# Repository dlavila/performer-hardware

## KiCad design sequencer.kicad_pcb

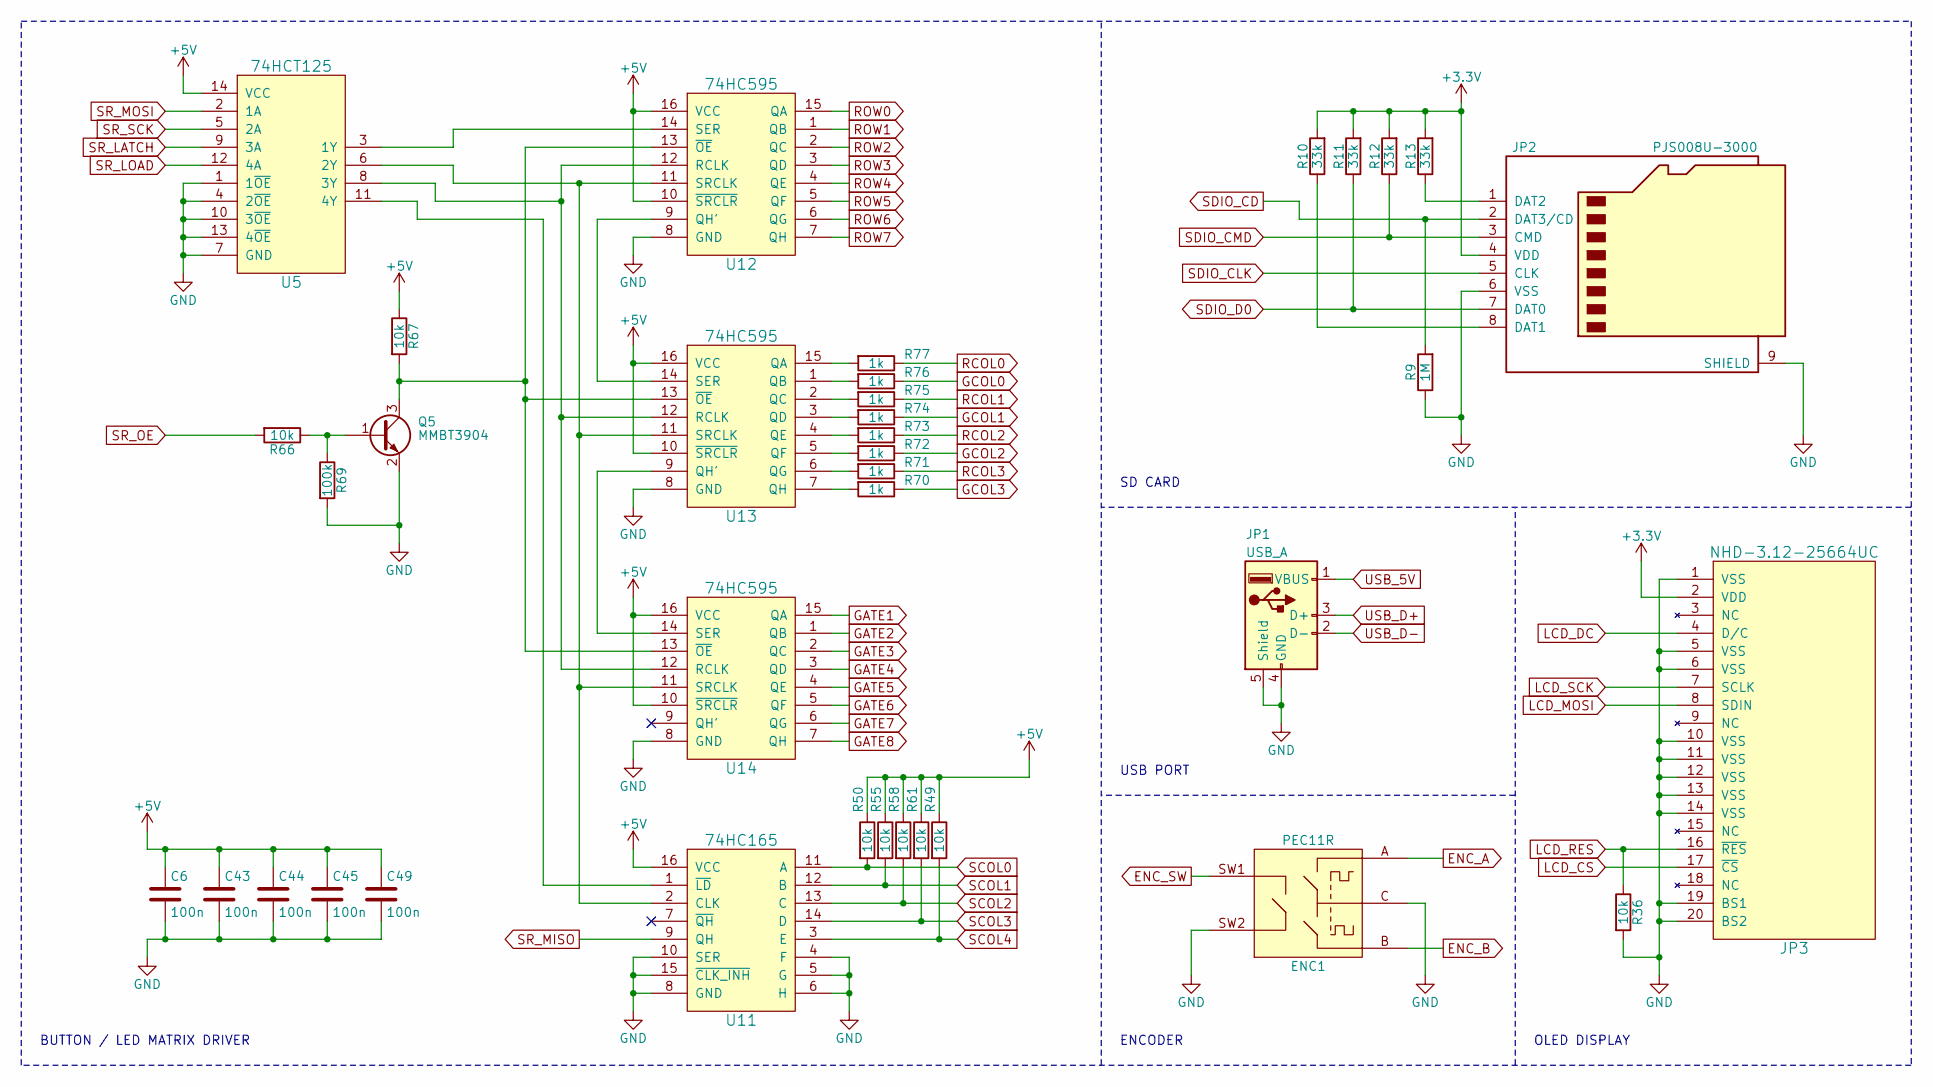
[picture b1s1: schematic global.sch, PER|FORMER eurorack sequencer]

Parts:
C6, C43, C44, C45, C49: 100n; C_0603
ENC1: PEC11R; ALPS_STEC12E08
JP1: USB_A; Kycon_USB_KUSBVLPX-AS1N
JP2: PJS008U-3000; PJS008U-3000-0
JP3: NHD-3.12-25664UC
Q5: MMBT3904; SOT-23
R9: 1M; R_0603
R10, R11, R12, R13: 33k; R_0603
R36, R49, R50, R55, R58, R61, R66, R67: 10k; R_0603
R69: 100k; R_0603
R70, R71, R72, R73, R74, R75, R76, R77: 1k; R_0603
U5: 74HCT125; SOIC-14_3.9x8.7mm_P1.27mm
U11: 74HC165; SOIC-16
U12, U13, U14: 74HC595; SOIC-16

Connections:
ENC_A: ENC1.A; also elsewhere on the board
ENC_B: ENC1.B; also elsewhere on the board
ENC_SW: ENC1.SW1; also elsewhere on the board
GATE1: U14.15 (QA); also elsewhere on the board
GATE2: U14.1 (QB); also elsewhere on the board
GATE3: U14.2 (QC); also elsewhere on the board
GATE4: U14.3 (QD); also elsewhere on the board
GATE5: U14.4 (QE); also elsewhere on the board
GATE6: U14.5 (QF); also elsewhere on the board
GATE7: U14.6 (QG); also elsewhere on the board
GATE8: U14.7 (QH); also elsewhere on the board
GCOL0: R76.1; also elsewhere on the board
GCOL1: R74.1; also elsewhere on the board
GCOL2: R72.1; also elsewhere on the board
GCOL3: R70.1; also elsewhere on the board
LCD_CS: JP3.17 (~CS); also elsewhere on the board
LCD_DC: JP3.4 (D/C); also elsewhere on the board
LCD_MOSI: JP3.8 (SDIN); also elsewhere on the board
LCD_RES: JP3.16 (~RES), R36.1; also elsewhere on the board
LCD_SCK: JP3.7 (SCLK); also elsewhere on the board
unnamed: JP2.1 (DAT2), R13.1
unnamed: JP2.8 (DAT1), R10.1
unnamed: Q5.1 (B), R66.1, R69.1
unnamed: Q5.3 (C), R67.2, U12.13 (~OE~), U13.13 (~OE~), U14.13 (~OE~)
unnamed: R70.2, U13.7 (QH)
unnamed: R71.2, U13.6 (QG)
unnamed: R72.2, U13.5 (QF)
unnamed: R73.2, U13.4 (QE)
unnamed: R74.2, U13.3 (QD)
unnamed: R75.2, U13.2 (QC)
unnamed: R76.2, U13.1 (QB)
unnamed: R77.2, U13.15 (QA)
unnamed: U5.11 (4Y), U11.1 (~LD~)
unnamed: U5.6 (2Y), U11.2 (CLK), U12.11 (SRCLK), U13.11 (SRCLK), U14.11 (SRCLK)
unnamed: U12.9 (QH'), U13.14 (SER)
unnamed: U5.8 (3Y), U12.12 (RCLK), U13.12 (RCLK), U14.12 (RCLK)
unnamed: U5.3 (1Y), U12.14 (SER)
unnamed: U13.9 (QH'), U14.14 (SER)
RCOL0: R77.1; also elsewhere on the board
RCOL1: R75.1; also elsewhere on the board
RCOL2: R73.1; also elsewhere on the board
RCOL3: R71.1; also elsewhere on the board
ROW0: U12.15 (QA); also elsewhere on the board
ROW1: U12.1 (QB); also elsewhere on the board
ROW2: U12.2 (QC); also elsewhere on the board
ROW3: U12.3 (QD); also elsewhere on the board
ROW4: U12.4 (QE); also elsewhere on the board
ROW5: U12.5 (QF); also elsewhere on the board
ROW6: U12.6 (QG); also elsewhere on the board
ROW7: U12.7 (QH); also elsewhere on the board
SCOL0: R50.2, U11.11 (A); also elsewhere on the board
SCOL1: R55.2, U11.12 (B); also elsewhere on the board
SCOL2: R58.2, U11.13 (C); also elsewhere on the board
SCOL3: R61.2, U11.14 (D); also elsewhere on the board
SCOL4: R49.2, U11.3 (E); also elsewhere on the board
SDIO_CD: JP2.2 (DAT3/CD), R9.2; also elsewhere on the board
SDIO_CLK: JP2.5 (CLK); also elsewhere on the board
SDIO_CMD: JP2.3 (CMD), R12.1; also elsewhere on the board
SDIO_D0: JP2.7 (DAT0), R11.1; also elsewhere on the board
SR_LATCH: U5.9 (3A); also elsewhere on the board
SR_LOAD: U5.12 (4A); also elsewhere on the board
SR_MISO: U11.9 (QH); also elsewhere on the board
SR_MOSI: U5.2 (1A); also elsewhere on the board
SR_OE: R66.2; also elsewhere on the board
SR_SCK: U5.5 (2A); also elsewhere on the board
USB_5V: JP1.1 (VBUS); also elsewhere on the board
USB_D+: JP1.3 (D+); also elsewhere on the board
USB_D-: JP1.2 (D-); also elsewhere on the board

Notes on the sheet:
BUTTON / LED MATRIX DRIVER
SD CARD
OLED DISPLAY
ENCODER
USB PORT

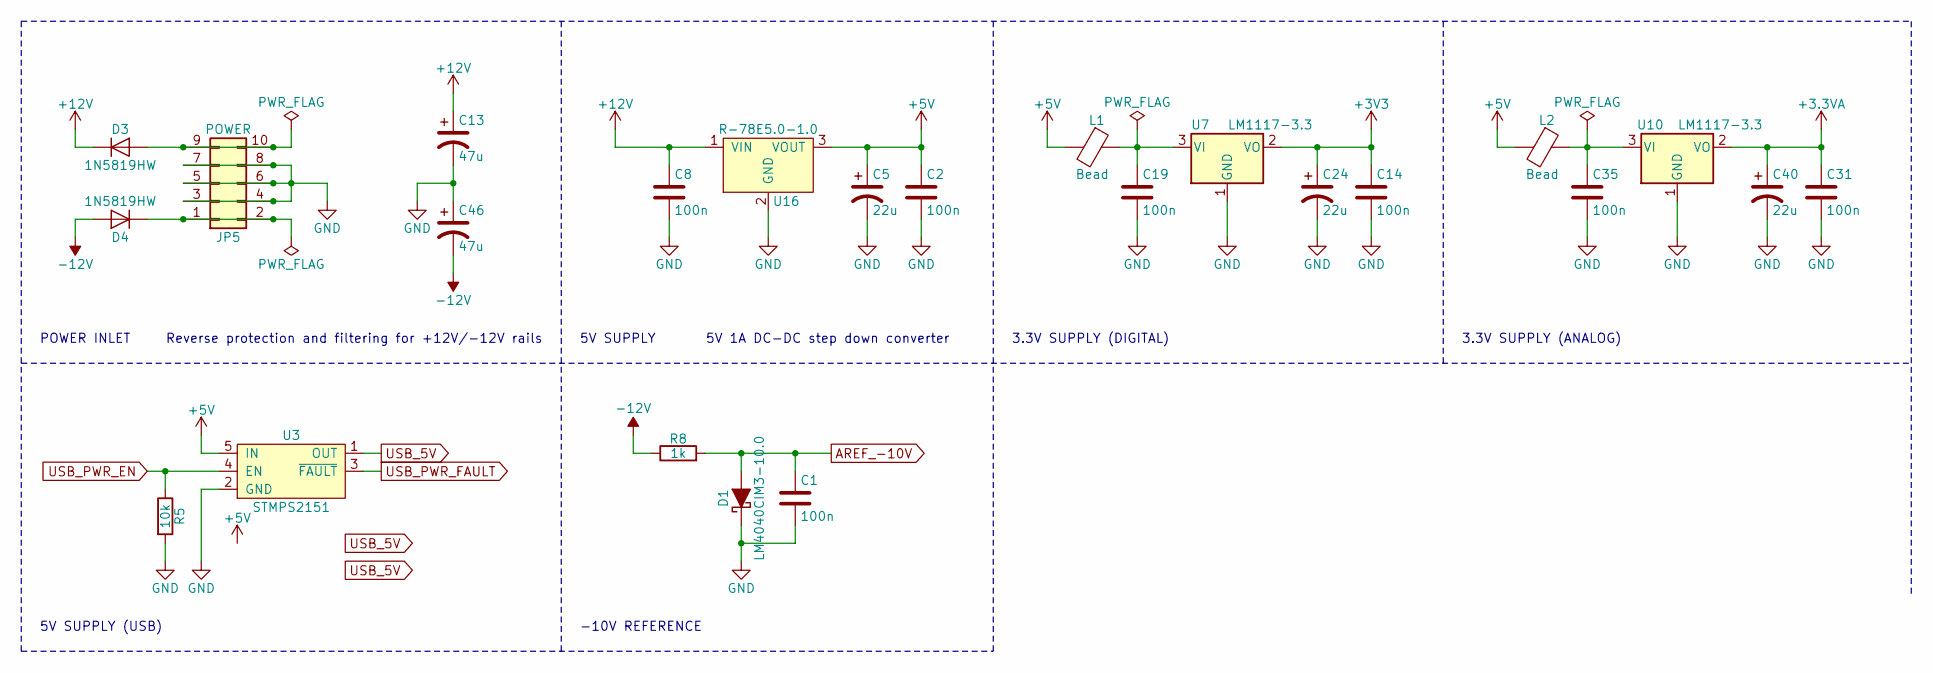
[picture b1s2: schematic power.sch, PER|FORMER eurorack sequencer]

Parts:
C1, C2, C8, C14, C19, C31, C35: 100n; C_0603
C5, C24, C40: 22u; CP_Elec_5x5.8
C13, C46: 47u; CP_Elec_6.3x5.7
D1: LM4040CIM3-10.0; SOT-23
D3, D4: 1N5819HW; D_SOD-123
JP5: POWER; PinHeader_2x05_P2.54mm_Vertical
L1, L2: Bead; R_0603
R5: 10k; R_0603
R8: 1k; R_0603
U3: STMPS2151; TSSOP-8_4.4x3mm_P0.65mm
U7, U10: LM1117-3.3; SOT-223-3_TabPin2
U16: R-78E5.0-1.0; R-78E-1.0

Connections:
+3.3VA: C31.1, C40.1, U10.2 (VO); also elsewhere on the board
+12V: C8.1, C13.1, D3.1 (K), U16.1 (VIN); also elsewhere on the board
-12V: C46.2, D4.2 (A), R8.1; also elsewhere on the board
AREF_-10V: C1.1, D1.2 (A), R8.2; also elsewhere on the board
unnamed: C19.1, L1.1, U7.3 (VI)
unnamed: C35.1, L2.1, U10.3 (VI)
unnamed: D3.2 (A), JP5.9, JP5.10
unnamed: D4.1 (K), JP5.1, JP5.2
USB_5V: U3.6, U3.7, U3.8; also elsewhere on the board
USB_PWR_EN: R5.1, U3.4 (EN); also elsewhere on the board

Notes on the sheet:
POWER INLET
Reverse protection and filtering for +12V/-12V rails
5V SUPPLY
5V 1A DC-DC step down converter
3.3V SUPPLY (DIGITAL)
3.3V SUPPLY (ANALOG)
5V SUPPLY (USB)
-10V REFERENCE

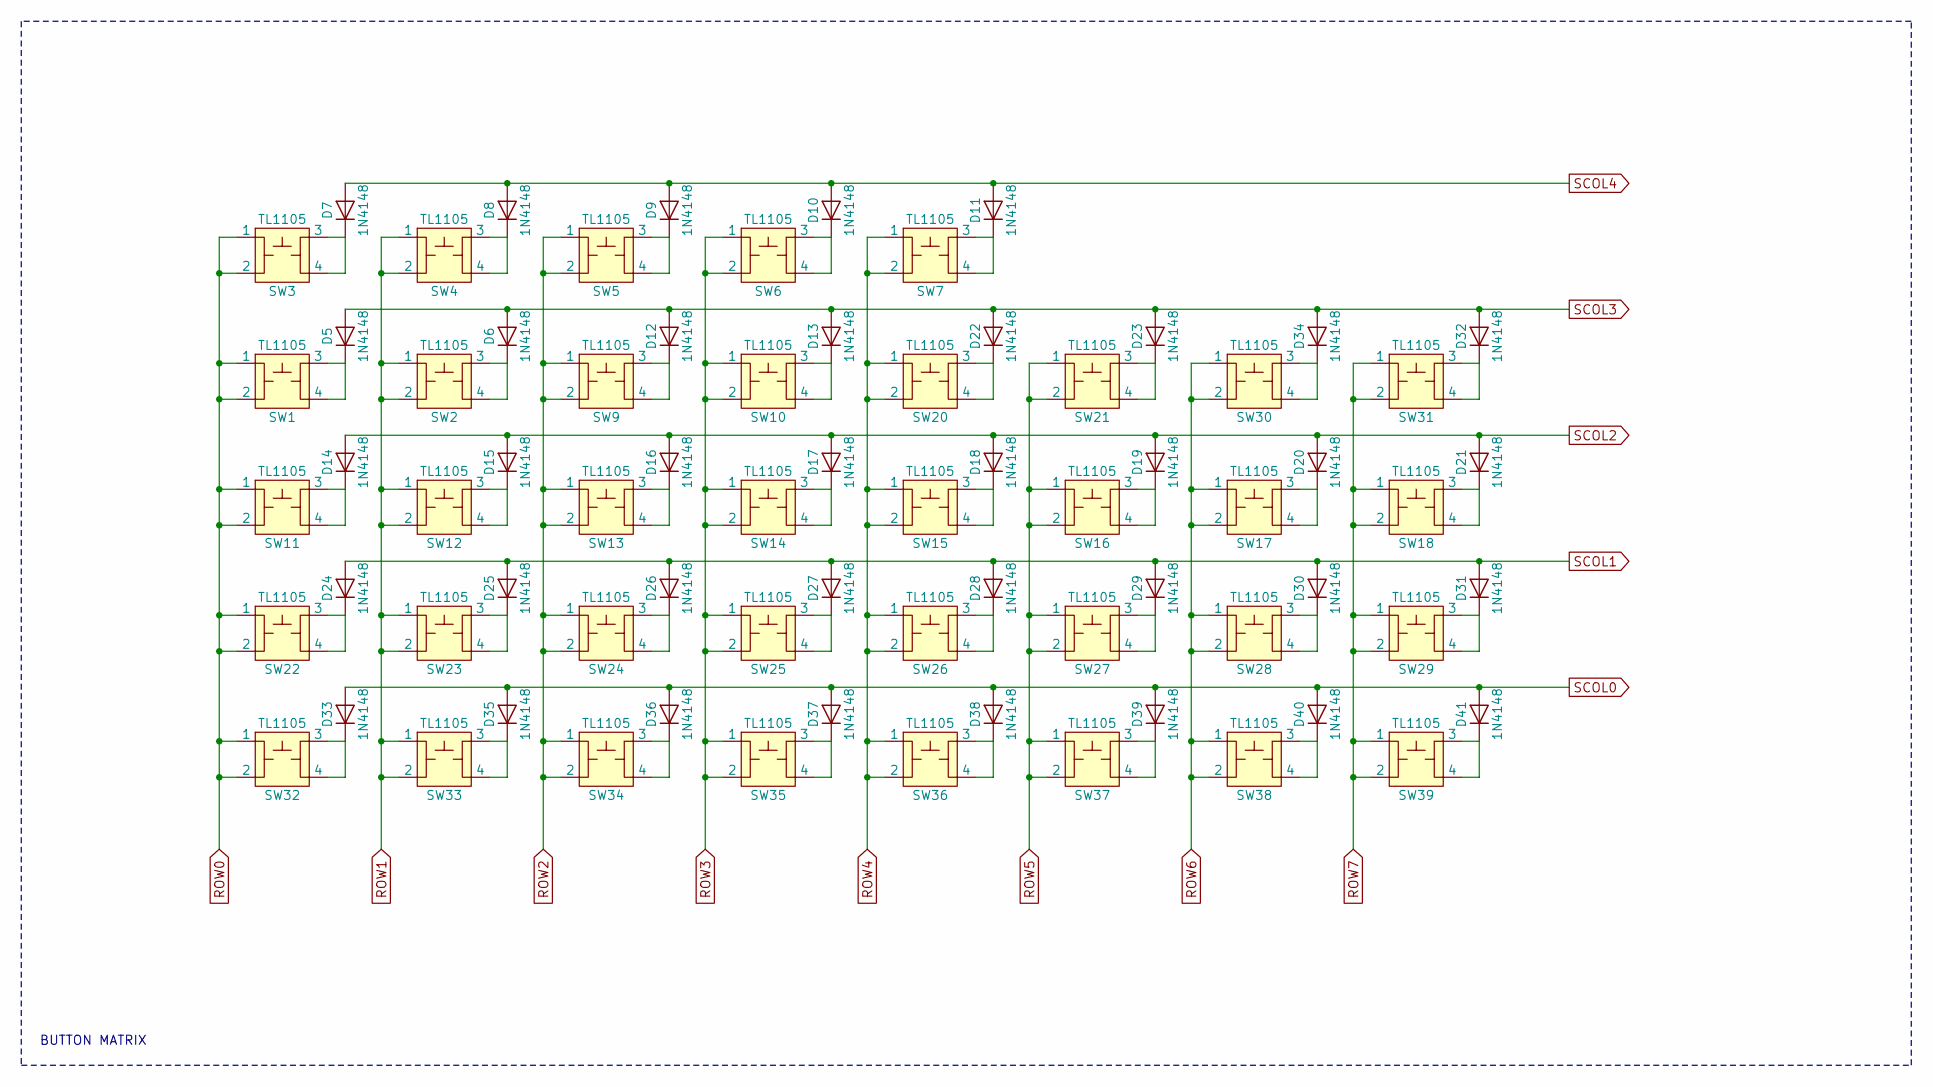
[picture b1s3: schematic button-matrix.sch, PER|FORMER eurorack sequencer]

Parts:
D5, D6, D7, D8, D9, D10, D11, D12, D13, D14, D15, D16, D17, D18, D19, D20, D21, D22, D23, D24, D25, D26, D27, D28, D29, D30, D31, D32, D33, D34, D35, D36, D37, D38, D39, D40, D41: 1N4148; D_SOD-123
SW1, SW2, SW3, SW4, SW5, SW6, SW7, SW9, SW10, SW11, SW12, SW13, SW14, SW15, SW16, SW17, SW18, SW20, SW21, SW22, SW23, SW24, SW25, SW26, SW27, SW28, SW29, SW30, SW31, SW32, SW33, SW34, SW35, SW36, SW37, SW38, SW39: TL1105; TL1105T

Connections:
unnamed: D5.1 (K), SW1.3, SW1.4
unnamed: D6.1 (K), SW2.3, SW2.4
unnamed: D7.1 (K), SW3.3, SW3.4
unnamed: D8.1 (K), SW4.3, SW4.4
unnamed: D9.1 (K), SW5.3, SW5.4
unnamed: D10.1 (K), SW6.3, SW6.4
unnamed: D11.1 (K), SW7.3, SW7.4
unnamed: D12.1 (K), SW9.3, SW9.4
unnamed: D13.1 (K), SW10.3, SW10.4
unnamed: D14.1 (K), SW11.3, SW11.4
unnamed: D15.1 (K), SW12.3, SW12.4
unnamed: D16.1 (K), SW13.3, SW13.4
unnamed: D17.1 (K), SW14.3, SW14.4
unnamed: D18.1 (K), SW15.3, SW15.4
unnamed: D19.1 (K), SW16.3, SW16.4
unnamed: D20.1 (K), SW17.3, SW17.4
unnamed: D21.1 (K), SW18.3, SW18.4
unnamed: D22.1 (K), SW20.3, SW20.4
unnamed: D23.1 (K), SW21.3, SW21.4
unnamed: D24.1 (K), SW22.3, SW22.4
unnamed: D25.1 (K), SW23.3, SW23.4
unnamed: D26.1 (K), SW24.3, SW24.4
unnamed: D27.1 (K), SW25.3, SW25.4
unnamed: D28.1 (K), SW26.3, SW26.4
unnamed: D29.1 (K), SW27.3, SW27.4
unnamed: D30.1 (K), SW28.3, SW28.4
unnamed: D31.1 (K), SW29.3, SW29.4
unnamed: D32.1 (K), SW31.3, SW31.4
unnamed: D33.1 (K), SW32.3, SW32.4
unnamed: D34.1 (K), SW30.3, SW30.4
unnamed: D35.1 (K), SW33.3, SW33.4
unnamed: D36.1 (K), SW34.3, SW34.4
unnamed: D37.1 (K), SW35.3, SW35.4
unnamed: D38.1 (K), SW36.3, SW36.4
unnamed: D39.1 (K), SW37.3, SW37.4
unnamed: D40.1 (K), SW38.3, SW38.4
unnamed: D41.1 (K), SW39.3, SW39.4
ROW0: SW1.1, SW1.2, SW3.1, SW3.2, SW11.1, SW11.2, SW22.1, SW22.2, SW32.1, SW32.2; also elsewhere on the board
ROW1: SW2.1, SW2.2, SW4.1, SW4.2, SW12.1, SW12.2, SW23.1, SW23.2, SW33.1, SW33.2; also elsewhere on the board
ROW2: SW5.1, SW5.2, SW9.1, SW9.2, SW13.1, SW13.2, SW24.1, SW24.2, SW34.1, SW34.2; also elsewhere on the board
ROW3: SW6.1, SW6.2, SW10.1, SW10.2, SW14.1, SW14.2, SW25.1, SW25.2, SW35.1, SW35.2; also elsewhere on the board
ROW4: SW7.1, SW7.2, SW15.1, SW15.2, SW20.1, SW20.2, SW26.1, SW26.2, SW36.1, SW36.2; also elsewhere on the board
ROW5: SW16.1, SW16.2, SW21.1, SW21.2, SW27.1, SW27.2, SW37.1, SW37.2; also elsewhere on the board
ROW6: SW17.1, SW17.2, SW28.1, SW28.2, SW30.1, SW30.2, SW38.1, SW38.2; also elsewhere on the board
ROW7: SW18.1, SW18.2, SW29.1, SW29.2, SW31.1, SW31.2, SW39.1, SW39.2; also elsewhere on the board
SCOL0: D33.2 (A), D35.2 (A), D36.2 (A), D37.2 (A), D38.2 (A), D39.2 (A), D40.2 (A), D41.2 (A); also elsewhere on the board
SCOL1: D24.2 (A), D25.2 (A), D26.2 (A), D27.2 (A), D28.2 (A), D29.2 (A), D30.2 (A), D31.2 (A); also elsewhere on the board
SCOL2: D14.2 (A), D15.2 (A), D16.2 (A), D17.2 (A), D18.2 (A), D19.2 (A), D20.2 (A), D21.2 (A); also elsewhere on the board
SCOL3: D5.2 (A), D6.2 (A), D12.2 (A), D13.2 (A), D22.2 (A), D23.2 (A), D32.2 (A), D34.2 (A); also elsewhere on the board
SCOL4: D7.2 (A), D8.2 (A), D9.2 (A), D10.2 (A), D11.2 (A); also elsewhere on the board

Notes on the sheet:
BUTTON MATRIX

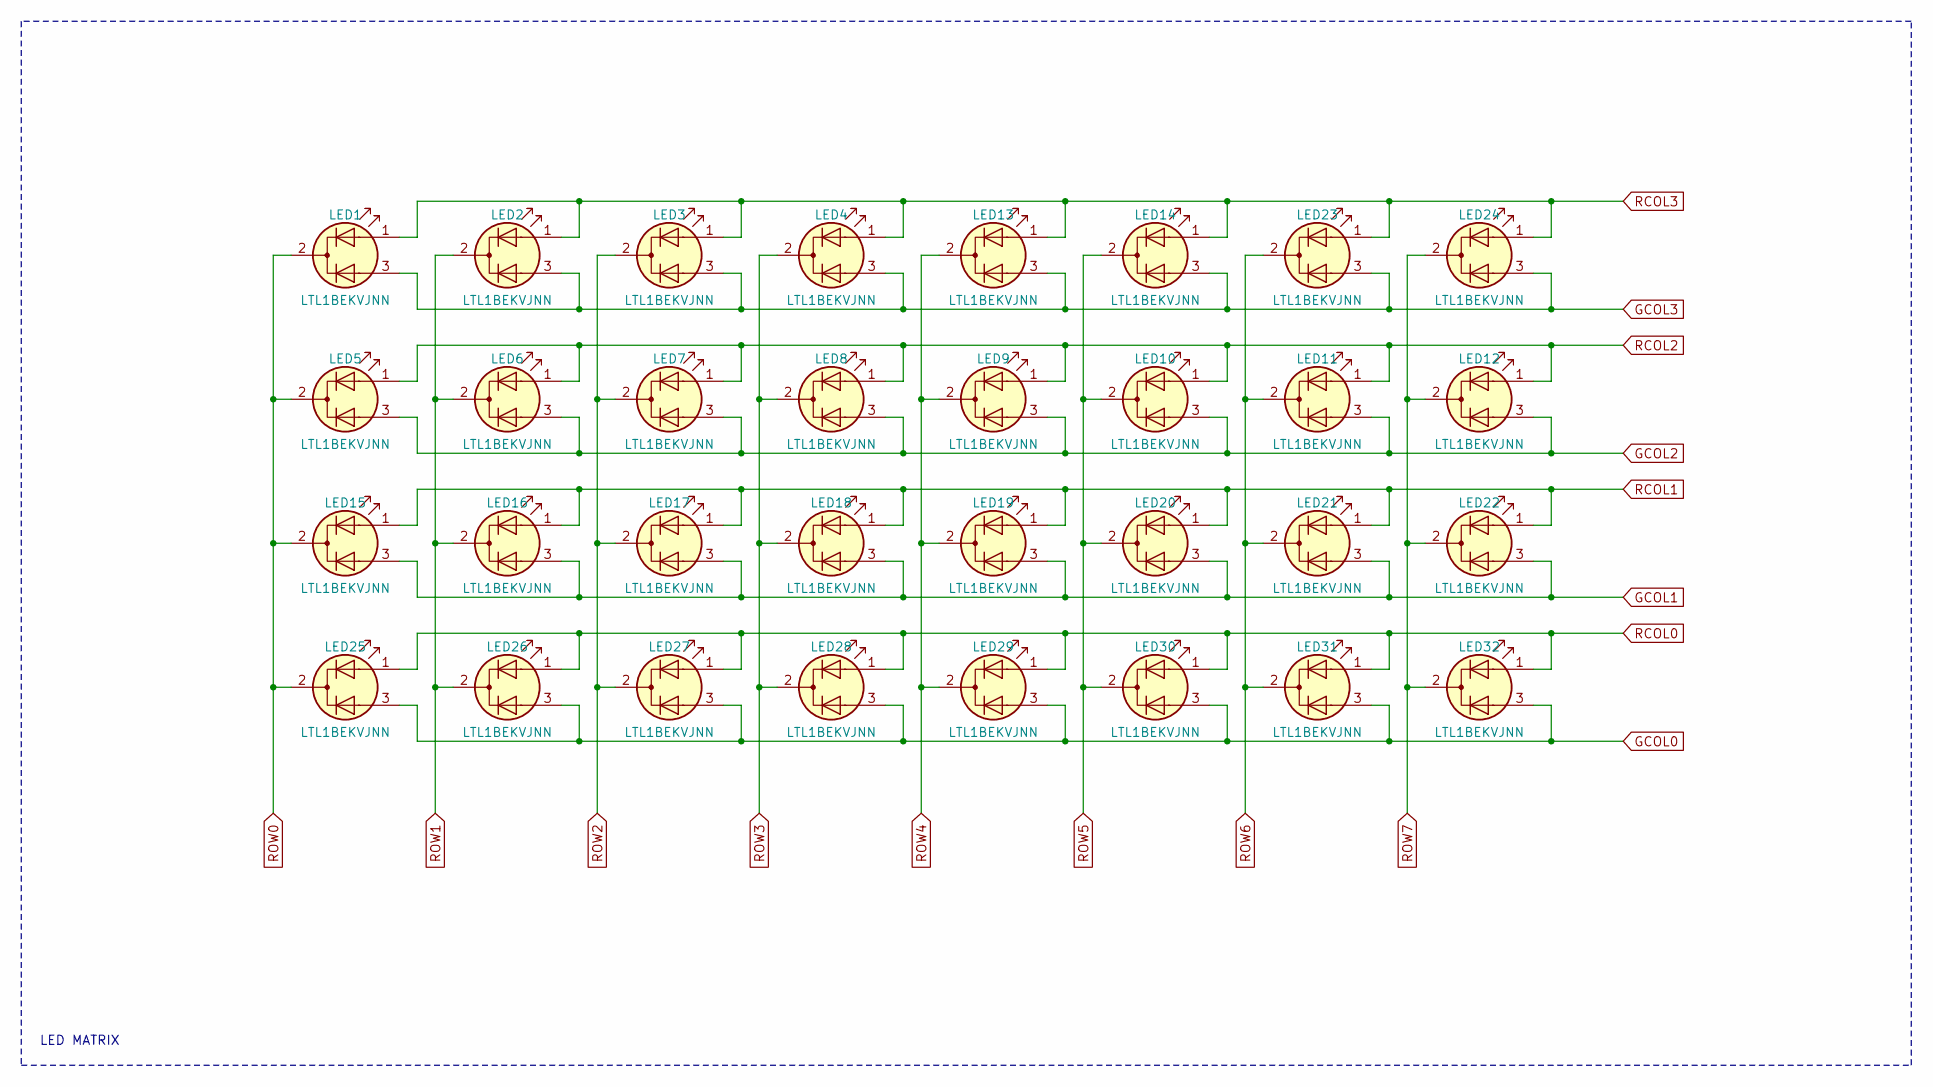
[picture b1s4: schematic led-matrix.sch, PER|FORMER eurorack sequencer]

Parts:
LED1, LED2, LED3, LED4, LED5, LED6, LED7, LED8, LED9, LED10, LED11, LED12, LED13, LED14, LED15, LED16, LED17, LED18, LED19, LED20, LED21, LED22, LED23, LED24, LED25, LED26, LED27, LED28, LED29, LED30, LED31, LED32: LTL1BEKVJNN

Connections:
GCOL0: LED25.3 (A2), LED26.3 (A2), LED27.3 (A2), LED28.3 (A2), LED29.3 (A2), LED30.3 (A2), LED31.3 (A2), LED32.3 (A2); also elsewhere on the board
GCOL1: LED15.3 (A2), LED16.3 (A2), LED17.3 (A2), LED18.3 (A2), LED19.3 (A2), LED20.3 (A2), LED21.3 (A2), LED22.3 (A2); also elsewhere on the board
GCOL2: LED5.3 (A2), LED6.3 (A2), LED7.3 (A2), LED8.3 (A2), LED9.3 (A2), LED10.3 (A2), LED11.3 (A2), LED12.3 (A2); also elsewhere on the board
GCOL3: LED1.3 (A2), LED2.3 (A2), LED3.3 (A2), LED4.3 (A2), LED13.3 (A2), LED14.3 (A2), LED23.3 (A2), LED24.3 (A2); also elsewhere on the board
RCOL0: LED25.1 (A1), LED26.1 (A1), LED27.1 (A1), LED28.1 (A1), LED29.1 (A1), LED30.1 (A1), LED31.1 (A1), LED32.1 (A1); also elsewhere on the board
RCOL1: LED15.1 (A1), LED16.1 (A1), LED17.1 (A1), LED18.1 (A1), LED19.1 (A1), LED20.1 (A1), LED21.1 (A1), LED22.1 (A1); also elsewhere on the board
RCOL2: LED5.1 (A1), LED6.1 (A1), LED7.1 (A1), LED8.1 (A1), LED9.1 (A1), LED10.1 (A1), LED11.1 (A1), LED12.1 (A1); also elsewhere on the board
RCOL3: LED1.1 (A1), LED2.1 (A1), LED3.1 (A1), LED4.1 (A1), LED13.1 (A1), LED14.1 (A1), LED23.1 (A1), LED24.1 (A1); also elsewhere on the board
ROW0: LED1.2 (K), LED5.2 (K), LED15.2 (K), LED25.2 (K); also elsewhere on the board
ROW1: LED2.2 (K), LED6.2 (K), LED16.2 (K), LED26.2 (K); also elsewhere on the board
ROW2: LED3.2 (K), LED7.2 (K), LED17.2 (K), LED27.2 (K); also elsewhere on the board
ROW3: LED4.2 (K), LED8.2 (K), LED18.2 (K), LED28.2 (K); also elsewhere on the board
ROW4: LED9.2 (K), LED13.2 (K), LED19.2 (K), LED29.2 (K); also elsewhere on the board
ROW5: LED10.2 (K), LED14.2 (K), LED20.2 (K), LED30.2 (K); also elsewhere on the board
ROW6: LED11.2 (K), LED21.2 (K), LED23.2 (K), LED31.2 (K); also elsewhere on the board
ROW7: LED12.2 (K), LED22.2 (K), LED24.2 (K), LED32.2 (K); also elsewhere on the board

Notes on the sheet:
LED MATRIX

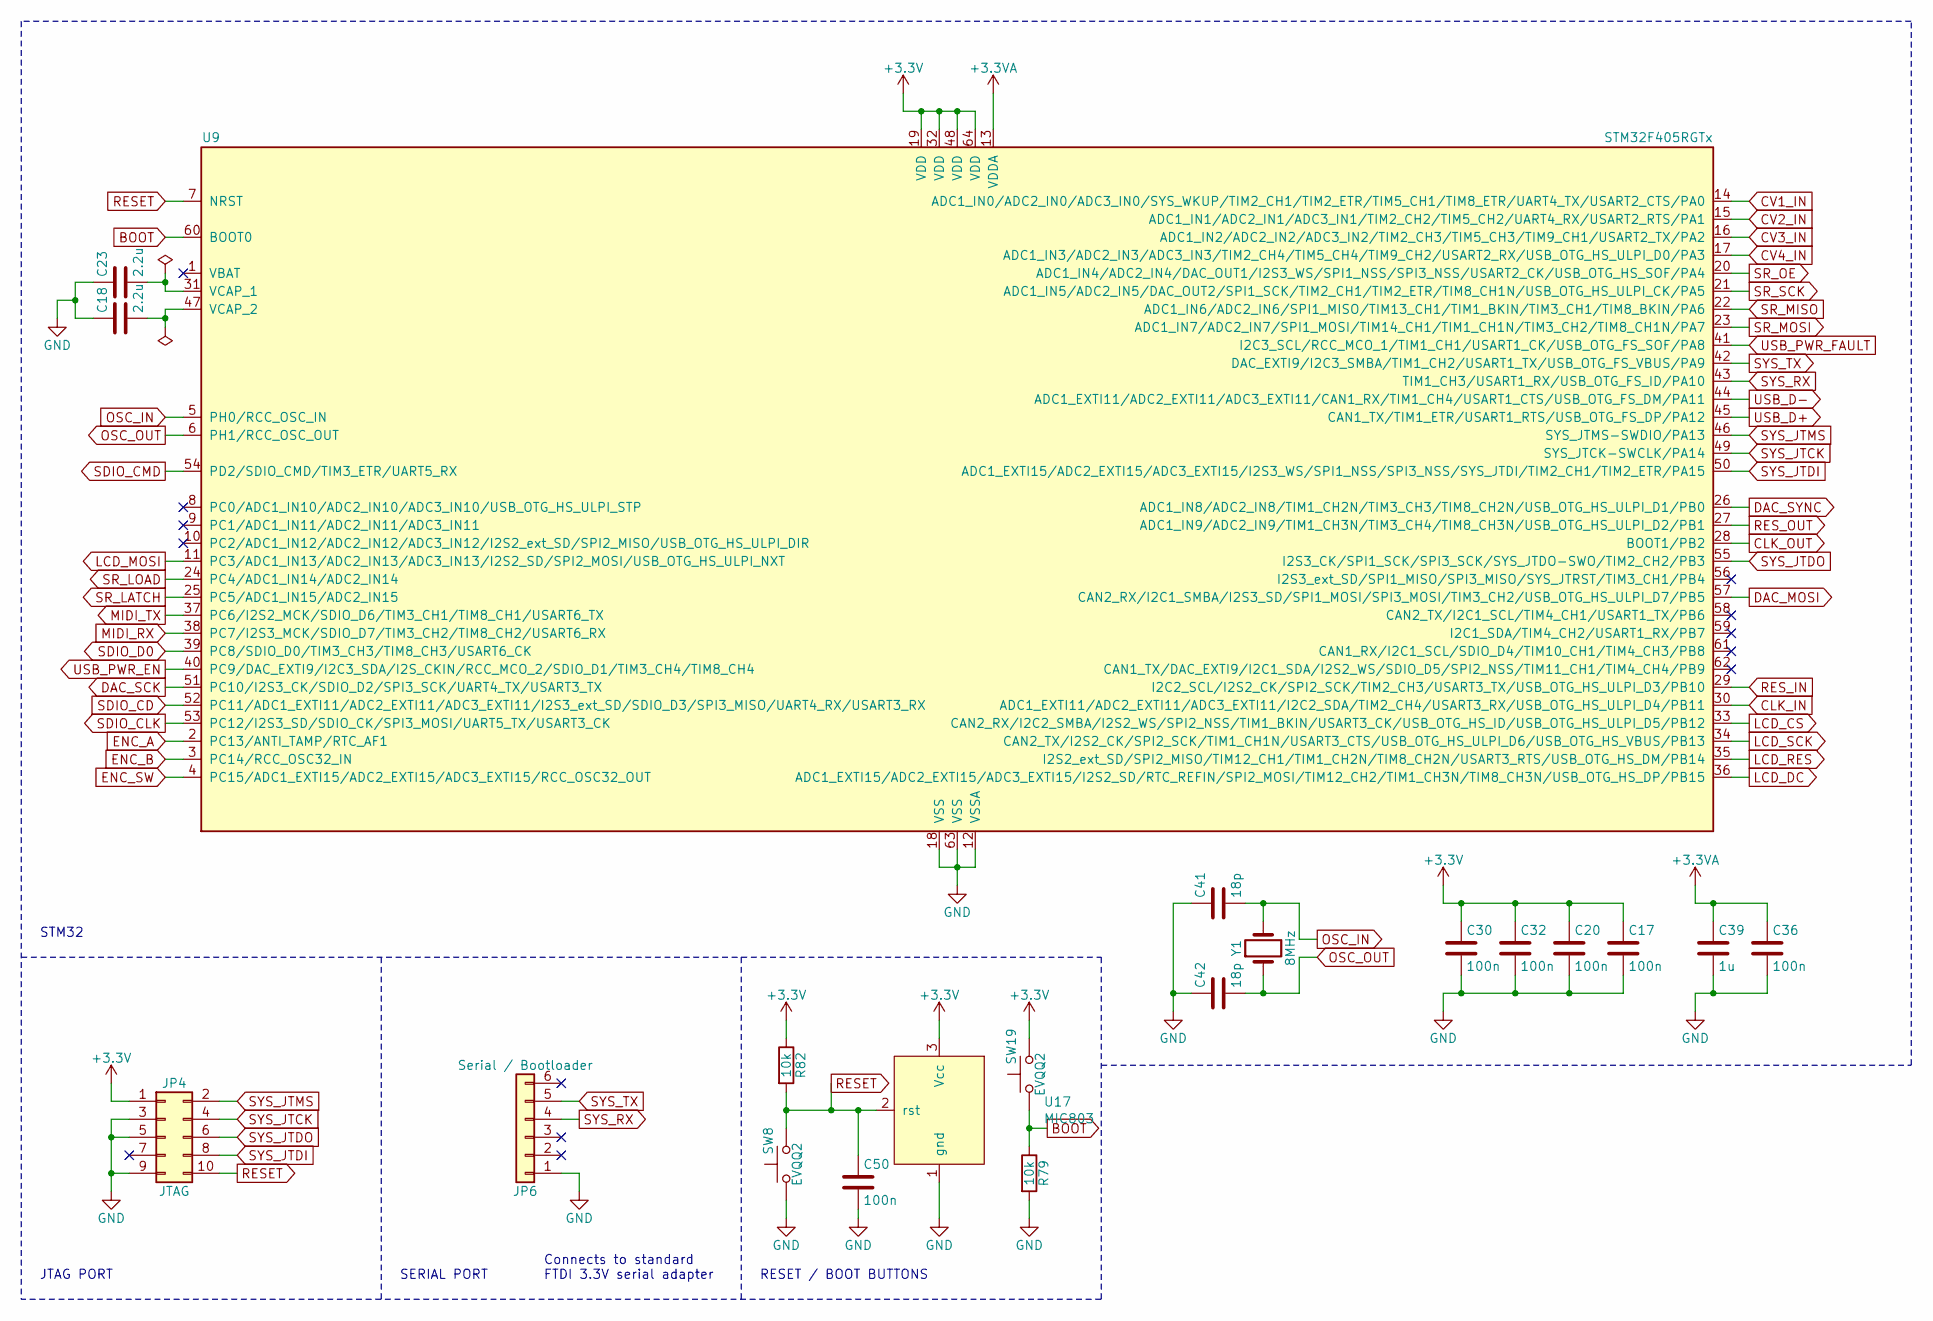
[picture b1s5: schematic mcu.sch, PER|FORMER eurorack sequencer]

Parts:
C17, C20, C30, C32, C36, C50: 100n; C_0603
C18, C23: 2.2u; C_0603
C39: 1u; C_0603
C41, C42: 18p; C_0603
JP4: JTAG; PinHeader_2x05_P1.27mm_Vertical
JP6: Serial / Bootloader; PinHeader_1x06_P2.54mm_Vertical
R79, R82: 10k; R_0603
SW8, SW19: EVQQ2; SW_SPST_EVQQ2
U9: STM32F405RGTx; LQFP-64_10x10mm_P0.5mm
U17: MIC803; SOT-23
Y1: 8MHz; Crystal_SMD_Abracon_ABM3-2Pin_5.0x3.2mm_HandSoldering

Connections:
+3.3VA: C36.1, C39.1, U9.13 (VDDA); also elsewhere on the board
BOOT: R79.1, SW19.1, U9.60 (BOOT0)
CLK_IN: U9.30 (ADC1_EXTI11/ADC2_EXTI11/ADC3_EXTI11/I2C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); also elsewhere on the board
CLK_OUT: U9.28 (BOOT1/PB2); also elsewhere on the board
CV1_IN: U9.14 (ADC1_IN0/ADC2_IN0/ADC3_IN0/SYS_WKUP/TIM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); also elsewhere on the board
CV2_IN: U9.15 (ADC1_IN1/ADC2_IN1/ADC3_IN1/TIM2_CH2/TIM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); also elsewhere on the board
CV3_IN: U9.16 (ADC1_IN2/ADC2_IN2/ADC3_IN2/TIM2_CH3/TIM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); also elsewhere on the board
CV4_IN: U9.17 (ADC1_IN3/ADC2_IN3/ADC3_IN3/TIM2_CH4/TIM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); also elsewhere on the board
DAC_MOSI: U9.57 (CAN2_RX/I2C1_SMBA/I2S3_SD/SPI1_MOSI/SPI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); also elsewhere on the board
DAC_SCK: U9.51 (PC10/I2S3_CK/SDIO_D2/SPI3_SCK/UART4_TX/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); also elsewhere on the board
DAC_SYNC: U9.26 (ADC1_IN8/ADC2_IN8/TIM1_CH2N/TIM3_CH3/TI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); also elsewhere on the board
ENC_A: U9.2 (PC13/ANTI_TAMP/RTC_AF1); also elsewhere on the board
ENC_B: U9.3 (PC14/RCC_OSC32_IN); also elsewhere on the board
ENC_SW: U9.4 (PC15/ADC1_EXTI15/ADC2_EXTI15/ADC3_EXTI1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); also elsewhere on the board
LCD_CS: U9.33 (CAN2_RX/I2C2_SMBA/I2S2_WS/SPI2_NSS/TIM1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); also elsewhere on the board
LCD_DC: U9.36 (ADC1_EXTI15/ADC2_EXTI15/ADC3_EXTI15/I2S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); also elsewhere on the board
LCD_MOSI: U9.11 (PC3/ADC1_IN13/ADC2_IN13/ADC3_IN13/I2S2_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); also elsewhere on the board
LCD_RES: U9.35 (I2S2_ext_SD/SPI2_MISO/TIM12_CH1/TIM1_CH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); also elsewhere on the board
LCD_SCK: U9.34 (CAN2_TX/I2S2_CK/SPI2_SCK/TIM1_CH1N/USAR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); also elsewhere on the board
MIDI_RX: U9.38 (PC7/I2S3_MCK/SDIO_D7/TIM3_CH2/TIM8_CH2/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); also elsewhere on the board
MIDI_TX: U9.37 (PC6/I2S2_MCK/SDIO_D6/TIM3_CH1/TIM8_CH1/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); also elsewhere on the board
unnamed: C18.2, U9.47 (VCAP_2)
unnamed: C23.2, U9.31 (VCAP_1)
OSC_IN: C41.2, U9.5 (PH0/RCC_OSC_IN), Y1.2
OSC_OUT: C42.2, U9.6 (PH1/RCC_OSC_OUT), Y1.1
RESET: C50.1, JP4.10, R82.2, SW8.2, U9.7 (NRST), U17.2 (rst)
RES_IN: U9.29 (I2C2_SCL/I2S2_CK/SPI2_SCK/TIM2_CH3/USAR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); also elsewhere on the board
RES_OUT: U9.27 (ADC1_IN9/ADC2_IN9/TIM1_CH3N/TIM3_CH4/TI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); also elsewhere on the board
SDIO_CD: U9.52 (PC11/ADC1_EXTI11/ADC2_EXTI11/ADC3_EXTI1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); also elsewhere on the board
SDIO_CLK: U9.53 (PC12/I2S3_SD/SDIO_CK/SPI3_MOSI/UART5_TX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); also elsewhere on the board
SDIO_CMD: U9.54 (PD2/SDIO_CMD/TIM3_ETR/UART5_RX); also elsewhere on the board
SDIO_D0: U9.39 (PC8/SDIO_D0/TIM3_CH3/TIM8_CH3/USART6_CK); also elsewhere on the board
SR_LATCH: U9.25 (PC5/ADC1_IN15/ADC2_IN15); also elsewhere on the board
SR_LOAD: U9.24 (PC4/ADC1_IN14/ADC2_IN14); also elsewhere on the board
SR_MISO: U9.22 (ADC1_IN6/ADC2_IN6/SPI1_MISO/TIM13_CH1/T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); also elsewhere on the board
SR_MOSI: U9.23 (ADC1_IN7/ADC2_IN7/SPI1_MOSI/TIM14_CH1/T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); also elsewhere on the board
SR_OE: U9.20 (ADC1_IN4/ADC2_IN4/DAC_OUT1/I2S3_WS/SPI1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); also elsewhere on the board
SR_SCK: U9.21 (ADC1_IN5/ADC2_IN5/DAC_OUT2/SPI1_SCK/TIM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); also elsewhere on the board
SYS_JTCK: JP4.4, U9.49 (SYS_JTCK-SWCLK/PA14)
SYS_JTDI: JP4.8, U9.50 (ADC1_EXTI15/ADC2_EXTI15/ADC3_EXTI15/I2S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)
SYS_JTDO: JP4.6, U9.55 (I2S3_CK/SPI1_SCK/SPI3_SCK/SYS_JTDO-SWO/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)
SYS_JTMS: JP4.2, U9.46 (SYS_JTMS-SWDIO/PA13)
SYS_RX: JP6.4, U9.43 (TIM1_CH3/USART1_RX/USB_OTG_FS_ID/PA10)
SYS_TX: JP6.5, U9.42 (DAC_EXTI9/I2C3_SMBA/TIM1_CH2/USART1_TX/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)
USB_D+: U9.45 (CAN1_TX/TIM1_ETR/USART1_RTS/USB_OTG_FS_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); also elsewhere on the board
USB_D-: U9.44 (ADC1_EXTI11/ADC2_EXTI11/ADC3_EXTI11/CAN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); also elsewhere on the board
USB_PWR_EN: U9.40 (PC9/DAC_EXTI9/I2C3_SDA/I2S_CKIN/RCC_MCO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); also elsewhere on the board

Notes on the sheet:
STM32
RESET / BOOT BUTTONS
SERIAL PORT
JTAG PORT
Connects to standard FTDI 3.3V serial adapter

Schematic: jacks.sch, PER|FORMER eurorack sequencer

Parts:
C7: 100n; C_0603
C9, C10, C21, C22: 1n; C_0603
C51, C52, C53, C54: ESD; C_0603
D2: 1N4148; D_SOD-123
D42, D43, D44, D45, D46, D47, D48, D49, D50, D51, D52, D53, D54, D55, D56, D57, D58, D59, D60, D61, D62, D63, D64, D65, D66, D67: LED; C_1206
D68, D69: 1N4148WS; D_SOD-123
J1, J2: PJ366ST; PJ366ST_Compact
J3, J4, J5, J6, J7, J8, J9, J10, J11, J12, J13, J14, J15, J16, J17, J18, J19, J20, J21, J22, J23, J24, J25, J26: PJ398SM; jack_thonk
J27: Conn_01x03_Female; PinHeader_1x03_P2.54mm_Vertical
Q1, Q2, Q3, Q4: MMBT3904; SOT-23
R1, R3, R4: 220; R_0603
R2, R6, R7, R19, R20: 10k; R_0603
R14, R17, R26, R27, R45, R46: 100k; R_0603
R15, R16: 1M; R_0603
R18, R21, R68, R78, R80, R81, R83, R84, R85, R86, R87, R88, R89, R90, R91, R92, R93, R94, R95, R96, R97, R98, R99, R100, R101, R102, R103, R104, R105, R106, R107, R108, R109, R110, R111, R112: 1k; R_0603
R30, R33, R37, R40: 200k; R_0603
R31, R32, R38, R39: 33k; R_0603
U1: VO0600T; SOIC-8_3.9x4.9mm_P1.27mm
U2: 74LV1T34; SOT-23-5
U6: MCP6004; SOIC-14_3.9x8.7mm_P1.27mm

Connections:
+3.3VA: C7.1, U6.4 (V+); also elsewhere on the board
+12V: J27.1; also elsewhere on the board
AREF_-10V: R30.2, R33.2, R37.2, R40.2; also elsewhere on the board
CLK_IN: Q1.3 (C), R6.2; also elsewhere on the board
CLK_OUT: R19.2; also elsewhere on the board
CV1: J12.3; also elsewhere on the board
CV1_IN: C22.1, R39.1, U6.1; also elsewhere on the board
CV2: J14.3; also elsewhere on the board
CV2_IN: C9.1, R31.1, U6.8; also elsewhere on the board
CV3: J16.3; also elsewhere on the board
CV3_IN: C10.1, R32.1, U6.7; also elsewhere on the board
CV4: J18.3; also elsewhere on the board
CV4_IN: C21.1, R38.1, U6.14; also elsewhere on the board
CV5: J20.3; also elsewhere on the board
CV6: J22.3; also elsewhere on the board
CV7: J24.3; also elsewhere on the board
CV8: J26.3; also elsewhere on the board
GATE1: R68.2; also elsewhere on the board
GATE2: R78.2; also elsewhere on the board
GATE3: R80.2; also elsewhere on the board
GATE4: R81.2; also elsewhere on the board
GATE5: R83.2; also elsewhere on the board
GATE6: R84.2; also elsewhere on the board
GATE7: R85.2; also elsewhere on the board
GATE8: R86.2; also elsewhere on the board
LED_VDD: J27.2, R87.2, R88.2, R89.2, R90.2, R91.2, R92.2, R93.2, R94.2, R95.2, R96.2, R97.2, R98.2, R99.2, R100.2, R101.2, R102.2, R103.2, R104.2, R105.2, R106.2, R107.2, R108.2, R109.2, R110.2, R111.2, R112.2
MIDI_RX: R2.2, U1.6; also elsewhere on the board
MIDI_TX: U2.2 (A); also elsewhere on the board
unnamed: C9.2, R26.1, R30.1, R31.2, U6.9 (-)
unnamed: C10.2, R27.1, R32.2, R33.1, U6.6 (-)
unnamed: C21.2, R37.1, R38.2, R45.1, U6.13 (-)
unnamed: C22.2, R39.2, R40.1, R46.1, U6.2 (-)
unnamed: C51.2, J7.3, R46.2
unnamed: C52.2, J8.3, R26.2
unnamed: C53.2, J10.3, R45.2
unnamed: C54.2, J9.3, R27.2
unnamed: D2.1 (K), R1.1, U1.2
unnamed: D2.2 (A), J1.3, U1.3
unnamed: D42.2, R87.1
unnamed: D43.2, R88.1
unnamed: D44.2, R89.1
unnamed: D45.2, R90.1
unnamed: D46.2, R91.1
unnamed: D47.2, R92.1
unnamed: D48.2, R93.1
unnamed: D49.2, R94.1
unnamed: D50.2, R95.1
unnamed: D51.2, R96.1
unnamed: D52.2, R97.1
unnamed: D53.2, R98.1
unnamed: D54.2, R99.1
unnamed: D55.2, R100.1
unnamed: D56.2, R101.1
unnamed: D57.2, R102.1
unnamed: D58.2, R103.1
unnamed: D59.2, R104.1
unnamed: D60.2, R105.1
unnamed: D61.2, R106.1
unnamed: D62.2, R107.1
unnamed: D63.2, R108.1
unnamed: D64.2, R109.1
unnamed: D65.2, R110.1
unnamed: D66.2, R111.1
unnamed: D67.2, R112.1
unnamed: D68.1, Q2.1 (B), R16.1, R17.1
unnamed: D69.1, Q1.1 (B), R14.1, R15.1
unnamed: J1.2, R1.2
unnamed: J2.2, R3.2
unnamed: J2.3, R4.2
unnamed: J3.3, R14.2
unnamed: J4.3, R17.2
unnamed: J5.3, Q3.3 (C), R18.2
unnamed: J6.3, Q4.3 (C), R21.2
unnamed: J11.3, R68.1
unnamed: J13.3, R78.1
unnamed: J15.3, R80.1
unnamed: J17.3, R81.1
unnamed: J19.3, R83.1
unnamed: J21.3, R84.1
unnamed: J23.3, R85.1
unnamed: J25.3, R86.1
unnamed: Q3.1 (B), R19.1
unnamed: Q4.1 (B), R20.1
unnamed: R4.1, U2.4 (Y)
RES_IN: Q2.3 (C), R7.2; also elsewhere on the board
RES_OUT: R20.2; also elsewhere on the board

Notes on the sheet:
CLOCK INPUTS
GATE OUTPUTS
CV OUTPUTS
MIDI INPUT/OUTPUT
CLOCK OUTPUTS
CV INPUTS
High signal threshold: 0.7V
High level: 5V
Inverting rail-to-rail opamp configuration, Input range [-5V,5V], Output range [3.3V,0V]

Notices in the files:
button-matrix.sch:
cc-by-nc-sa
sequencer.kicad_pcb:
cc-by-nc-sa Simon Kallweit 2020
